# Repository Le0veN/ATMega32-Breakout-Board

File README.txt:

ATMega32 Breakout Board

License
-
Copyright Alex AUngurencei 2013.

This repository contains the design files for the ATMega32 Breakout Board  and is
licensed under the CERN OHL v. 1.2.

You may redistribute and modify this project under the terms of the CERN
OHL v.1.2. (http://ohwr.org/cernohl). This documentation is distributed WITHOUT
ANY EXPRESS OR IMPLIED WARRANTY, INCLUDING OF MERCHANTABILITY, SATISFACTORY
QUALITY AND FITNESS FOR A PARTICULAR PURPOSE. Please see the CERN OHL v.1.2 for
applicable conditions

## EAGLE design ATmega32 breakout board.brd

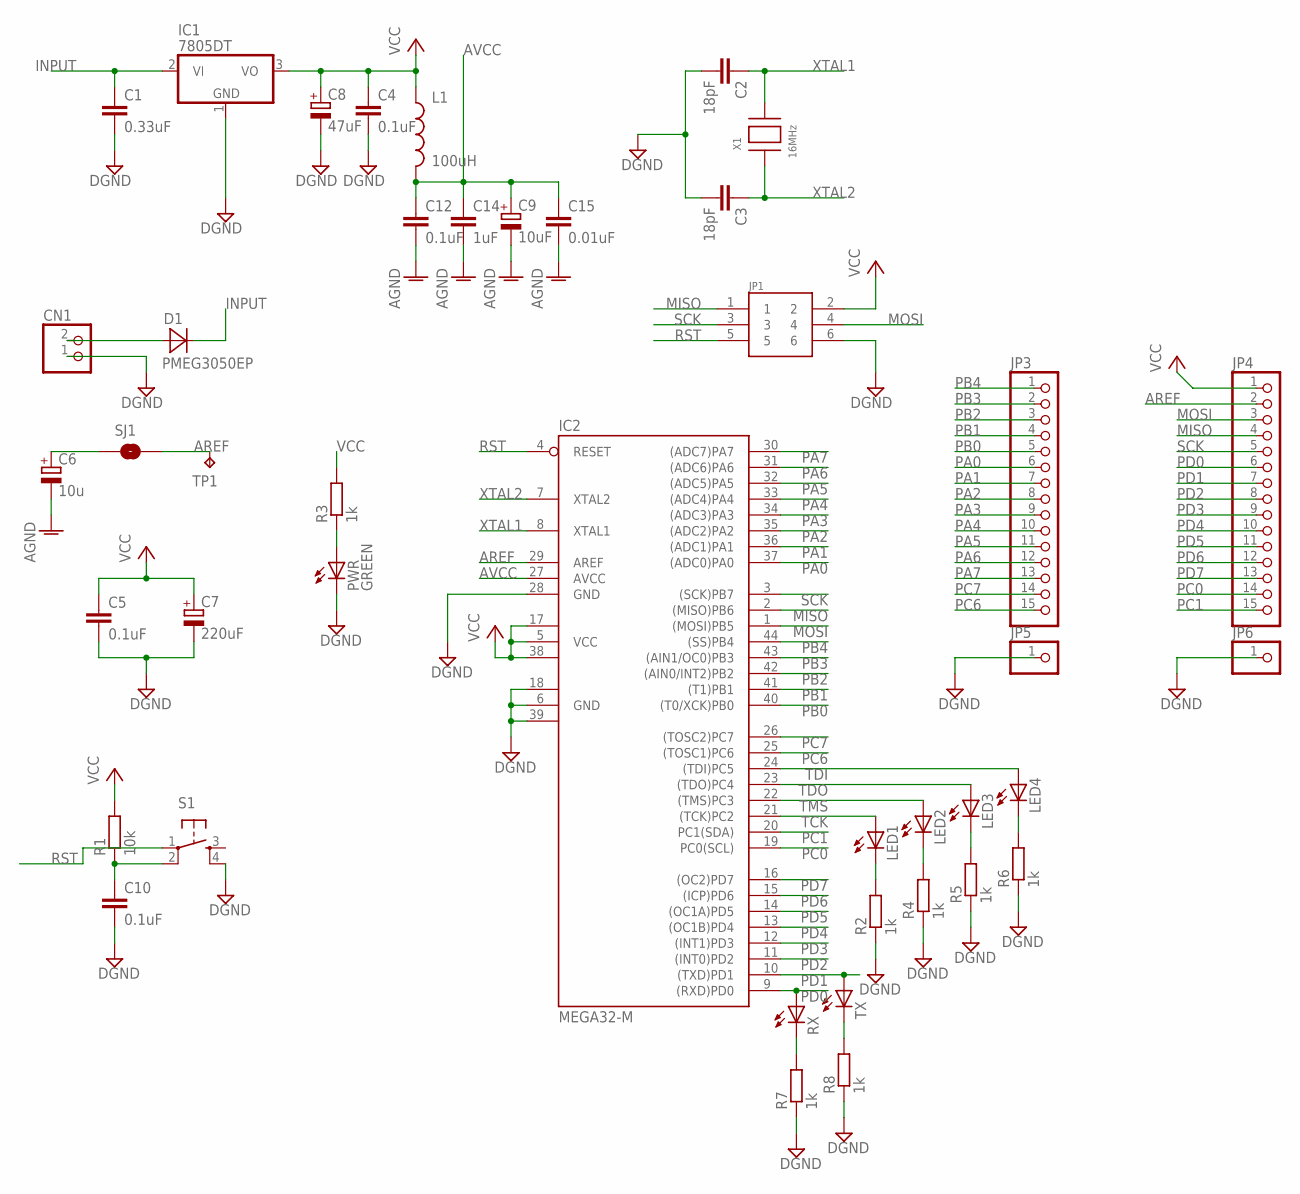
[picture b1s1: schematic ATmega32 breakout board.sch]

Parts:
C1: 0.33uF; C0603
C2, C3: 18pF; C0603
C4, C5, C10, C12: 0.1uF; C0603
C6: 10u; PANASONIC_A
C7: 220uF; E2,5-5
C8: 47uF; E2,5-5
C9: 10uF; E2-4
C14: 1uF; C0603
C15: 0.01uF; C0603
CN1: JST_2PIN-THM-RA; JST-PH-2-THM-RA
D1: PMEG3050EP; SMA
IC1: 7805DT; TO252
IC2: MEGA32-M; MLF44
JP1: M03X2; 2X3-SHROUDED
JP3, JP4: PINHD-1X15-CB; 1X15-CB
JP5, JP6: PINHD-1X1CB; 1X01-CLEANBIG
L1: 100uH; 0805
LED1, LED2, LED3, LED4: LEDCHIPLED_0603; CHIPLED_0603
PWR: GREEN; CHIPLED_0805
R1: 10k; R0603
R2, R4, R5, R6, R7, R8: 1k; R0402
R3: 1k; R0603
RX: LEDCHIPLED_0603; CHIPLED_0603
S1: TAC_SWITCHSMD; TACTILE_SWITCH_SMD
SJ1: SOLDERJUMPER-OLDTRACE; SJ_2S-TRACE
TP1: TPTP10R; TP10R
TX: LEDCHIPLED_0603; CHIPLED_0603
X1: 16MHz; NX5032

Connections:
AGND: C6.-, C9.-, C12.2, C14.2, C15.2
AREF: IC2.29 (AREF), JP4.2, SJ1.2, TP1.TP
AVCC: C9.+, C12.1, C14.1, C15.1, IC2.27 (AVCC), L1.2
GND: C1.2, C2.2, C3.2, C4.2, C5.2, C7.-, C8.-, C10.2, CN1.1 (2), IC1.1 (GND), IC2.6 (GND), IC2.18 (GND1), IC2.28 (GND), IC2.39 (GND2), JP1.6, JP5.1, JP6.1, PWR.C, R2.1, R4.1, R5.1, R6.1, R7.1, R8.1, S1.4
INPUT: C1.1, D1.C, IC1.2 (VI)
MISO: IC2.2 ((MISO)PB6), JP1.1, JP4.4
MOSI: IC2.1 ((MOSI)PB5), JP1.4, JP4.3
unnamed: PWR.A, R3.1
unnamed: C10.1, R1.1, S1.2
unnamed: CN1.2 (1), D1.A
unnamed: LED1.C, R2.2
unnamed: C6.+, SJ1.1
unnamed: LED2.C, R4.2
unnamed: LED3.C, R5.2
unnamed: LED4.C, R6.2
unnamed: R7.2, RX.C
unnamed: R8.2, TX.C
PA0: IC2.37 ((ADC0)PA0), JP3.6
PA1: IC2.36 ((ADC1)PA1), JP3.7
PA2: IC2.35 ((ADC2)PA2), JP3.8
PA3: IC2.34 ((ADC3)PA3), JP3.9
PA4: IC2.33 ((ADC4)PA4), JP3.10
PA5: IC2.32 ((ADC5)PA5), JP3.11
PA6: IC2.31 ((ADC6)PA6), JP3.12
PA7: IC2.30 ((ADC7)PA7), JP3.13
PB0: IC2.40 ((T0/XCK)PB0), JP3.5
PB1: IC2.41 ((T1)PB1), JP3.4
PB2: IC2.42 ((AIN0/INT2)PB2), JP3.3
PB3: IC2.43 ((AIN1/OC0)PB3), JP3.2
PB4: IC2.44 ((SS)PB4), JP3.1
PC0: IC2.19 (PC0(SCL)), JP4.14
PC1: IC2.20 (PC1(SDA)), JP4.15
PC6: IC2.25 ((TOSC1)PC6), JP3.15
PC7: IC2.26 ((TOSC2)PC7), JP3.14
PD0: IC2.9 ((RXD)PD0), JP4.6, RX.A
PD1: IC2.10 ((TXD)PD1), JP4.7, TX.A
PD2: IC2.11 ((INT0)PD2), JP4.8
PD3: IC2.12 ((INT1)PD3), JP4.9
PD4: IC2.13 ((OC1B)PD4), JP4.10
PD5: IC2.14 ((OC1A)PD5), JP4.11
PD6: IC2.15 ((ICP)PD6), JP4.12
PD7: IC2.16 ((OC2)PD7), JP4.13
RST: IC2.4 (RESET), JP1.5, S1.1
SCK: IC2.3 ((SCK)PB7), JP1.3, JP4.5
TCK: IC2.21 ((TCK)PC2), LED1.A
TDI: IC2.24 ((TDI)PC5), LED4.A
TDO: IC2.23 ((TDO)PC4), LED3.A
TMS: IC2.22 ((TMS)PC3), LED2.A
VCC: C4.1, C5.1, C7.+, C8.+, IC1.3 (VO), IC2.5 (VCC), IC2.17 (VCC1), IC2.38 (VCC2), JP1.2, JP4.1, L1.1, R1.2, R3.2
XTAL1: C2.1, IC2.8 (XTAL1), X1.P$2
XTAL2: C3.1, IC2.7 (XTAL2), X1.P$1

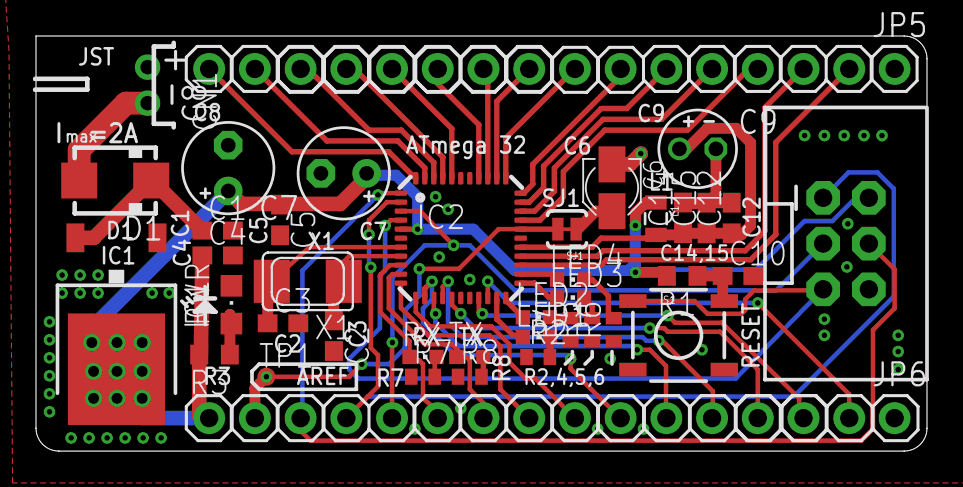
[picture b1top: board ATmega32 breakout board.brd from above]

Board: 2 copper layers, 49.5 x 23.1 mm, 42 parts (0 on the bottom side), 51 nets.

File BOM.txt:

Partlist exported from D:/Fuhrer/Google Drive/WORK/Projects/Hardware/ATmega/324P 20AU BkBoard/ATmega324P 20AU breakout board.sch at 19.04.2014 1:11:52

Part Value      Device                Package            Description                                   MF MPN           OC_FARNELL OC_NEWARK PROD_ID    TP_SIGNAL_NAME
C1   0.33uF     C-EUC0603             C0603              CAPACITOR, European symbol                                                                                   
C2   18pF       C-EUC0603             C0603              CAPACITOR, European symbol                                                                                   
C3   18pF       C-EUC0603             C0603              CAPACITOR, European symbol                                                                                   
C4   0.1uF      C-EUC0603             C0603              CAPACITOR, European symbol                                                                                   
C5   0.1uF      C-EUC0603             C0603              CAPACITOR, European symbol                                                                                   
C6   10u        CPOL-EUA              PANASONIC_A        POLARIZED CAPACITOR, European symbol                                                                         
C7   220uF      CPOL-EUE2.5-5         E2,5-5             POLARIZED CAPACITOR, European symbol                                                                         
C8   47uF       CPOL-EUE2.5-5         E2,5-5             POLARIZED CAPACITOR, European symbol                                                                         
C9   10uF       CPOL-EUE2-4           E2-4               POLARIZED CAPACITOR, European symbol                                                                         
C10  0.1uF      C-EUC0603             C0603              CAPACITOR, European symbol                                                                                   
C12  0.1uF      C-EUC0603             C0603              CAPACITOR, European symbol                                                                                   
C14  1uF        C-EUC0603             C0603              CAPACITOR, European symbol                                                                                   
C15  0.01uF     C-EUC0603             C0603              CAPACITOR, European symbol                                                                                   
CN1             JST_2PIN-THM-RA       JST-PH-2-THM-RA    JST 2-Pin Connectors of various flavors                                                                      
D1   PMEG3050EP MBRA340T3             SMA                Surface Mount Schottky Power Rectifier                                                                       
IC1  7805DT     7805DT                TO252              Positive VOLTAGE REGULATOR                                                                                   
IC2  MEGA32-M   MEGA32-M              MLF44              MICROCONTROLLER                                  ATMEGA32-16MU 1455108    58M3733                            
JP1             M03X2                 2X3-SHROUDED       2x3 .1" header.                                                                     CONN-10681               
JP3             PINHD-1X15-CB         1X15-CB            PIN HEADER                                                                                                   
JP4             PINHD-1X15-CB         1X15-CB            PIN HEADER                                                                                                   
JP5             PINHD-1X1CB           1X01-CLEANBIG      Pin header 1x1 for 0.1" spacing                                                                              
JP6             PINHD-1X1CB           1X01-CLEANBIG      Pin header 1x1 for 0.1" spacing                                                                              
L1   100uH      INDUCTOR0805          0805               Inductors                                                                                                    
LED1            LEDCHIPLED_0603       CHIPLED_0603       LED                                                                                                          
LED2            LEDCHIPLED_0603       CHIPLED_0603       LED                                                                                                          
LED3            LEDCHIPLED_0603       CHIPLED_0603       LED                                                                                                          
LED4            LEDCHIPLED_0603       CHIPLED_0603       LED                                                                                                          
PWR  GREEN      LEDCHIPLED_0805       CHIPLED_0805       LED                                                                                                          
R1   10k        R-EU_R0603            R0603              RESISTOR, European symbol                                                                                    
R2   1k         R-EU_R0402            R0402              RESISTOR, European symbol                                                                                    
R3   1k         R-EU_R0603            R0603              RESISTOR, European symbol                                                                                    
R4   1k         R-EU_R0402            R0402              RESISTOR, European symbol                                                                                    
R5   1k         R-EU_R0402            R0402              RESISTOR, European symbol                                                                                    
R6   1k         R-EU_R0402            R0402              RESISTOR, European symbol                                                                                    
R7   1k         R-EU_R0402            R0402              RESISTOR, European symbol                                                                                    
R8   1k         R-EU_R0402            R0402              RESISTOR, European symbol                                                                                    
RX              LEDCHIPLED_0603       CHIPLED_0603       LED                                                                                                          
S1              TAC_SWITCHSMD         TACTILE_SWITCH_SMD Momentary Switch                                                                                             
SJ1             SOLDERJUMPER-OLDTRACE SJ_2S-TRACE        Solder Jumper                                                                                                
TP1  TPTP10R    TPTP10R               TP10R              Test pad                                                                                                     
TX              LEDCHIPLED_0603       CHIPLED_0603       LED                                                                                                          
X1   16MHz      XTALNX5032            NX5032             Low cost SMT crystals, no capacitors included

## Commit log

2014-04-18 Breakout for ATMega32

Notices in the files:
parts and their libraries:
SparkFun-Passives: Licensing: CC v3.0 Share-Alike You are welcome to use this library for commercial purposes.
